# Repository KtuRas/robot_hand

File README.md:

# ROBOT EL
## Akış diyagramı:

## Devre tasarımı:

## Katkıda bulunanlar:

Alper Tuna

Ömer Çavdar

Ayberk Sungurtaş

Oğuzhan Mursallı

Hasan Eyuboğlu

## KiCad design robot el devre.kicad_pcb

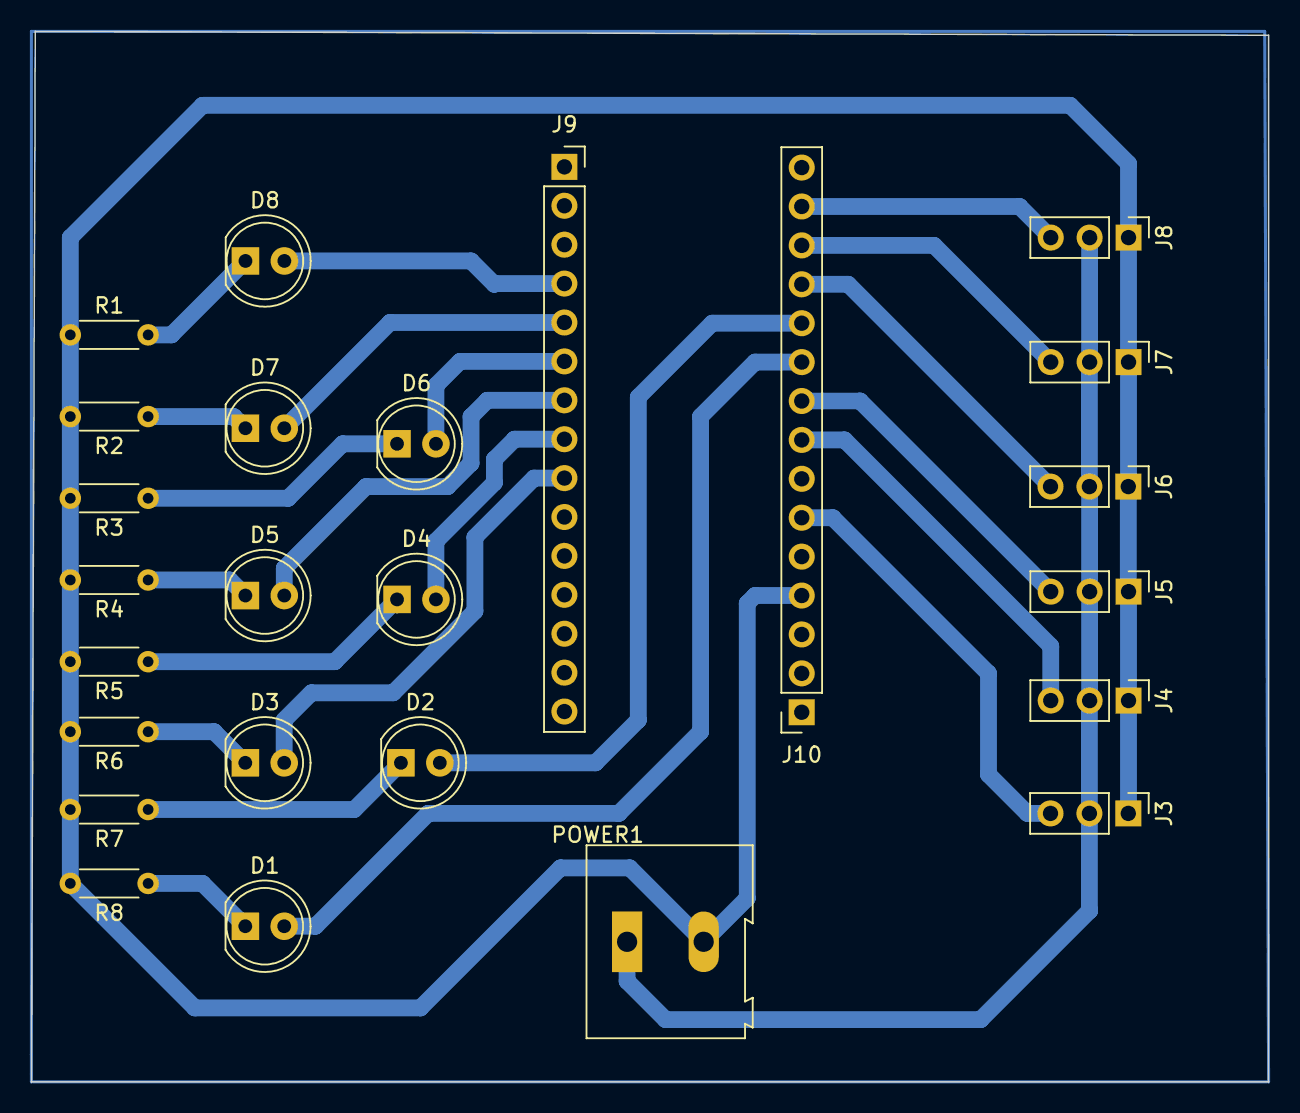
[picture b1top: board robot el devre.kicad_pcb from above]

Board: 2 copper layers, 80.8 x 68.6 mm, 25 parts (0 on the bottom side), 24 nets.

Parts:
D1, D2, D3, D4, D5, D6, D7, D8: LED; LED_D5.0mm
J3, J4, J5, J6, J7, J8: Conn_01x03_Pin; PinHeader_1x03_P2.54mm_Vertical
J9, J10: Conn_01x15; PinSocket_1x15_P2.54mm_Vertical
POWER1: Conn_01x02_Socket; TerminalBlock_Altech_AK300-2_P5.00mm
R1, R2, R3, R4, R5, R6, R7, R8: R; R_Axial_DIN0204_L3.6mm_D1.6mm_P5.08mm_Horizontal

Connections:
/+5V: J3.2, J4.2, J5.2, J6.2, J7.2, J8.2, POWER1.1
/A0: D8.2 (A), J9.4
/A1: D7.2 (A), J9.5
/A2: D6.2 (A), J9.6
/A3: D5.2 (A), J9.7
/A4: D4.2 (A), J9.8
/A5: D3.2 (A), J9.9
/D3: J3.3, J10.6
/D5: J4.3, J10.8
/D6: J5.3, J10.9
/D7: D1.2 (A), J10.10
/D8: D2.2 (A), J10.11
/D9: J6.3, J10.12
/D10: J7.3, J10.13
/D11: J8.3, J10.14
/GND: J3.1, J4.1, J5.1, J6.1, J7.1, J8.1, J9.14, J10.4, POWER1.2, R1.1, R2.2, R3.2, R4.2, R5.2, R6.2, R7.2, R8.2
unnamed: D1.1 (K), R8.1
unnamed: D2.1 (K), R7.1
unnamed: D3.1 (K), R6.1
unnamed: D4.1 (K), R5.1
unnamed: D5.1 (K), R4.1
unnamed: D6.1 (K), R3.1
unnamed: D7.1 (K), R2.1
unnamed: D8.1 (K), R1.2

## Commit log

2023-09-17 Add files via upload
    Arduino Nano code for communication via pc
2023-09-21 Added LED interface for finger and wrist movement
2023-10-17 Python code update for usage on Windows
2023-12-11 code rearrangement
2024-05-22 Create robot_hand_circuit_design
2024-05-22 robot_hand_circuit_design
2024-05-22 dddddddddd
2024-05-22 Robot el devresinin devre ve PCB tasarımı
2024-05-22 repo arrangement
